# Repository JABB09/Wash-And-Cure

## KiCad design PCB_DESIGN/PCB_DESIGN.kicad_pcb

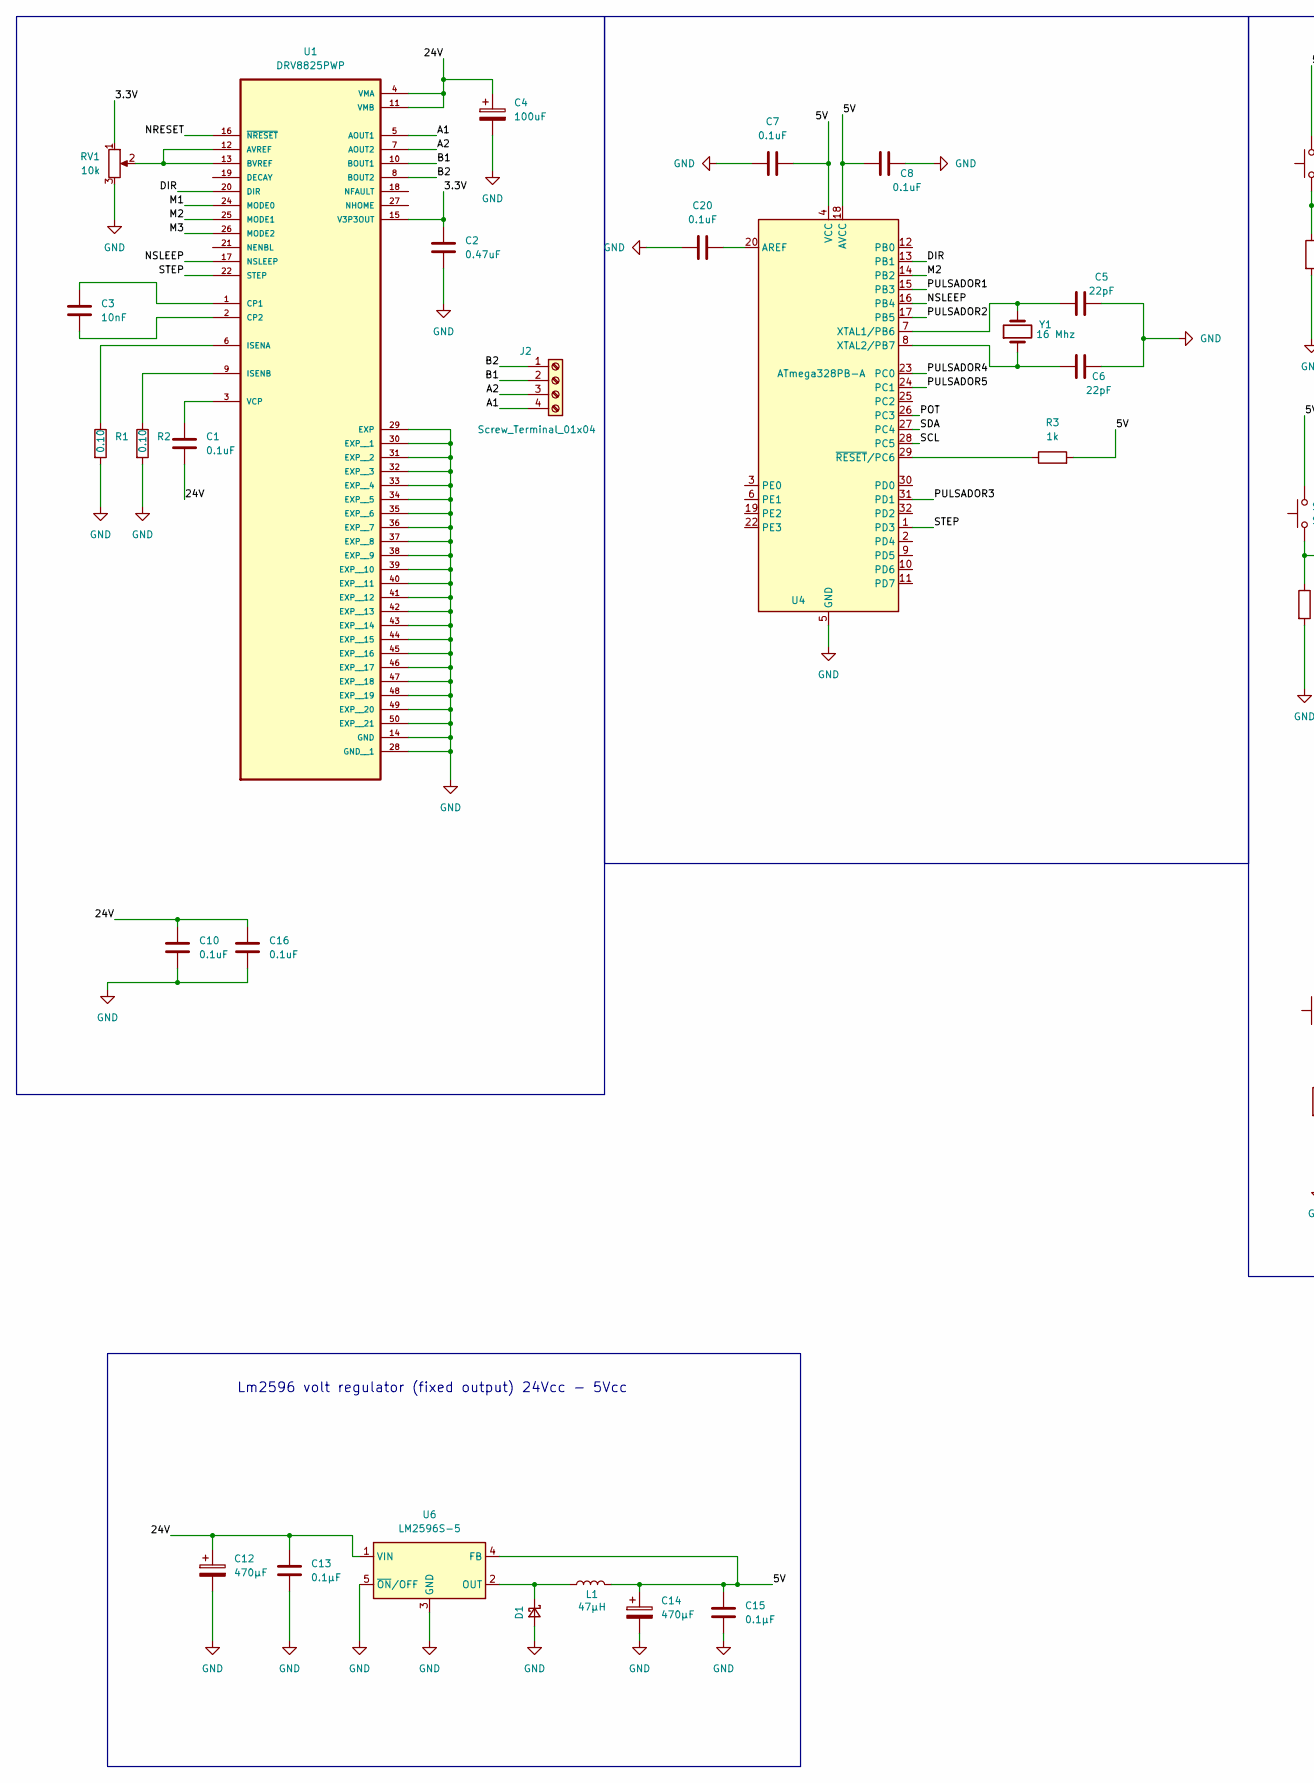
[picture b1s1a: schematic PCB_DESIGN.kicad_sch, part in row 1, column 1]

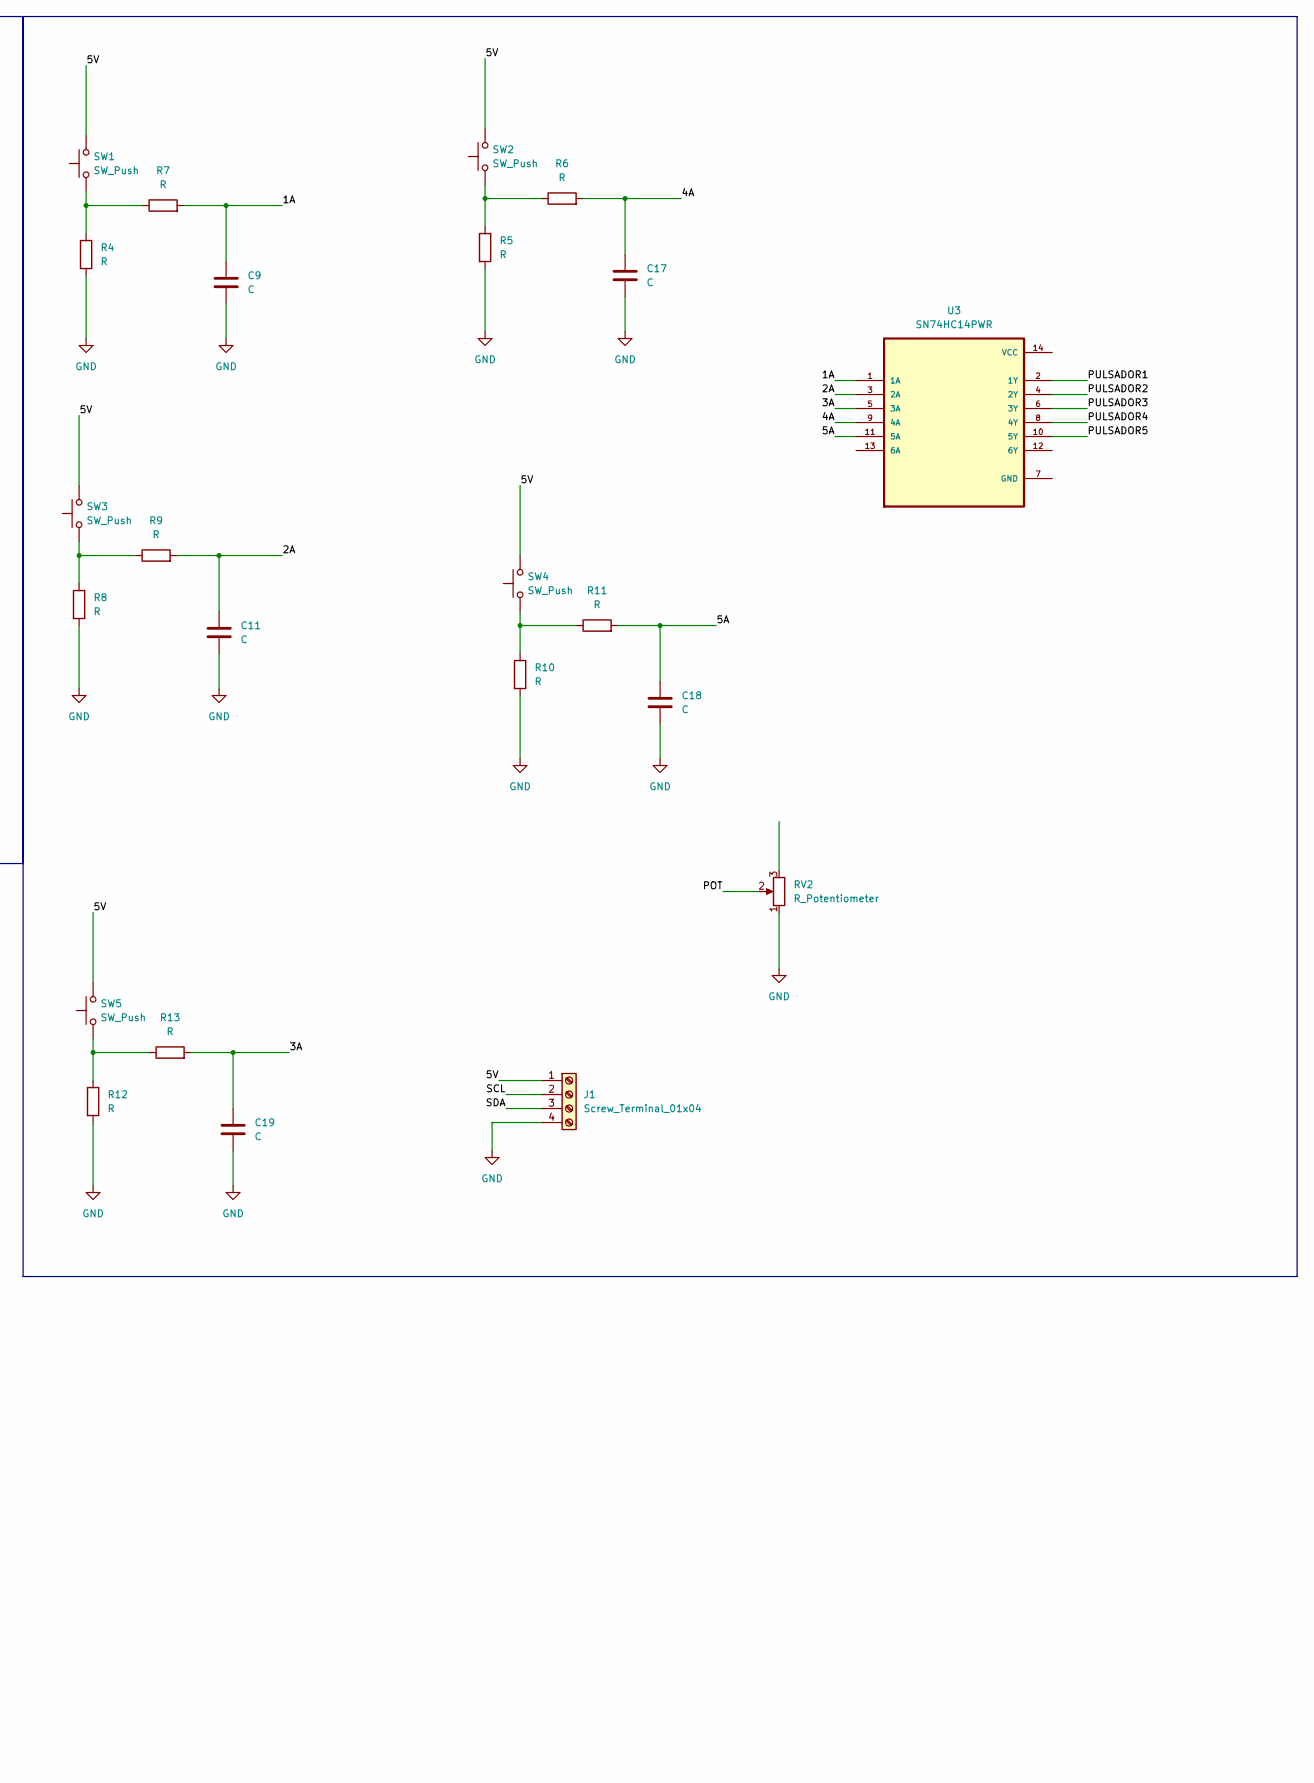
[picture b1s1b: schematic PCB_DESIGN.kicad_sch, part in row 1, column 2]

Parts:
C1, C7, C8, C10, C16, C20: 0.1uF; C_0603_1608Metric_Pad1.08x0.95mm_HandSolder
C2: 0.47uF; C_0603_1608Metric_Pad1.08x0.95mm_HandSolder
C3: 10nF; C_0603_1608Metric_Pad1.08x0.95mm_HandSolder
C4: 100uF; CP_Elec_4x5.3
C5, C6: 22pF; C_0603_1608Metric_Pad1.08x0.95mm_HandSolder
C9, C11, C17, C18, C19: C; C_0603_1608Metric_Pad1.08x0.95mm_HandSolder
C12, C14: 470μF; CP_Elec_4x5.3
C13, C15: 0.1μF; C_0603_1608Metric_Pad1.08x0.95mm_HandSolder
D1: D_Schottky_Small; D_SMA
J1, J2: Screw_Terminal_01x04; PinHeader_1x04_P2.54mm_Vertical
L1: 47μH; IND_SRR1240-470M
R1, R2: 0.10; R_0603_1608Metric_Pad0.98x0.95mm_HandSolder
R3: 1k; R_0603_1608Metric_Pad0.98x0.95mm_HandSolder
R4, R5, R6, R7, R8, R9, R10, R11, R12, R13: R; R_0603_1608Metric_Pad0.98x0.95mm_HandSolder
RV1: 10k; Potentiometer_Bourns_3314J_Vertical
RV2: R_Potentiometer; PinHeader_1x03_P2.54mm_Vertical
SW1, SW2, SW3, SW4, SW5: SW_Push; PinHeader_1x02_P2.54mm_Vertical
U1: DRV8825PWP; IC_TPS61196PWPRQ1
U3: SN74HC14PWR; SOP65P640X120-14N
U4: ATmega328PB-A; TQFP-32_7x7mm_P0.8mm
U6: LM2596S-5; TO-263-5_TabPin3
Y1: 16 Mhz; Crystal_SMD_0603-2Pin_6.0x3.5mm

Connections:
/1A: C9.2, R7.2, U3.1 (1A)
/2A: C11.2, R9.2, U3.3 (2A)
/3.3V: C2.1, RV1.1, U1.15 (V3P3OUT)
/3A: C19.2, R13.2, U3.5 (3A)
/4A: C17.2, R6.2, U3.9 (4A)
/5A: C18.2, R11.2, U3.11 (5A)
/5V: C7.2, C8.1, C14.1, C15.1, J1.1, L1.2, R3.2, SW1.2, SW2.2, SW3.2, SW4.2, SW5.2, U4.4 (VCC), U4.18 (AVCC), U6.4 (FB)
/24V: C1.2, C4.1, C10.1, C12.1, C13.1, C16.1, U1.4 (VMA), U1.11 (VMB), U6.1 (VIN)
/A1: J2.4, U1.5 (AOUT1)
/A2: J2.3, U1.7 (AOUT2)
/B1: J2.2, U1.10 (BOUT1)
/B2: J2.1, U1.8 (BOUT2)
/DIR: U1.20 (DIR), U4.13 (PB1)
/M1: U1.24 (MODE0)
/M2: U1.25 (MODE1), U4.14 (PB2)
/M3: U1.26 (MODE2)
/NRESET: U1.16 (~NRESET)
/NSLEEP: U1.17 (NSLEEP), U4.16 (PB4)
/POT: RV2.2, U4.26 (PC3)
/PULSADOR1: U3.2 (1Y), U4.15 (PB3)
/PULSADOR2: U3.4 (2Y), U4.17 (PB5)
/PULSADOR3: U3.6 (3Y), U4.31 (PD1)
/PULSADOR4: U3.8 (4Y), U4.23 (PC0)
/PULSADOR5: U3.10 (5Y), U4.24 (PC1)
/SCL: J1.2, U4.28 (PC5)
/SDA: J1.3, U4.27 (PC4)
/STEP: U1.22 (STEP), U4.1 (PD3)
GND: C2.2, C4.2, C5.2, C6.2, C7.1, C8.2, C9.1, C10.2, C11.1, C12.2, C13.2, C14.2, C15.2, C16.2, C17.1, C18.1, C19.1, C20.1, D1.2 (A), J1.4, R1.2, R2.2, R4.2, R5.2, R8.2, R10.2, R12.2, RV1.3, RV2.1, U1.14 (GND), U1.28 (GND__1), U1.29 (EXP), U1.30 (EXP__1), U1.31 (EXP__2), U1.32 (EXP__3), U1.33 (EXP__4), U1.34 (EXP__5), U1.35 (EXP__6), U1.36 (EXP__7), U1.37 (EXP__8), U1.38 (EXP__9), U1.39 (EXP__10), U1.40 (EXP__11), U1.41 (EXP__12), U1.42 (EXP__13), U1.43 (EXP__14), U1.44 (EXP__15), U1.45 (EXP__16), U1.46 (EXP__17), U1.47 (EXP__18), U1.48 (EXP__19), U1.49 (EXP__20), U1.50 (EXP__21), U4.5 (GND), U4.21 (GND), U6.3 (GND), U6.5 (~ON/OFF)
unnamed: D1.1 (K), L1.1, U6.2 (OUT)
unnamed: R4.1, R7.1, SW1.1
unnamed: R5.1, R6.1, SW2.1
unnamed: R8.1, R9.1, SW3.1
unnamed: R10.1, R11.1, SW4.1
unnamed: R12.1, R13.1, SW5.1
unnamed: RV1.2, U1.12 (AVREF), U1.13 (BVREF)
unnamed: C3.2, U1.1 (CP1)
unnamed: C3.1, U1.2 (CP2)
unnamed: R1.1, U1.6 (ISENA)
unnamed: R2.1, U1.9 (ISENB)
unnamed: C1.1, U1.3 (VCP)
unnamed: C20.2, U4.20 (AREF)
unnamed: C5.1, U4.7 (XTAL1/PB6), Y1.2
unnamed: C6.1, U4.8 (XTAL2/PB7), Y1.1
unnamed: R3.1, U4.29 (~RESET/PC6)

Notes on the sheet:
Lm2596 volt regulator (fixed output) 24Vcc - 5Vcc

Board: 2 copper layers, 49 parts (0 on the bottom side), 41 nets, no tracks yet.

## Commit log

2024-08-29 Primer Commit
2024-08-29 Se agrega submodulo de librerias al proyecto
2024-08-29 Actualización de librería
2024-08-29 Actualización submodulo
2024-09-01 Actualizacion
2024-09-01 Actualización
2024-09-05 Se actualiza el esquematico de la pcb
2024-09-05 Actualizacion de librerias
2024-09-06 Se actualiza el esquematico y se manda a pcb
2024-09-06 Actualización librería
2024-09-06 Se agregan pines de programación
2024-09-06 Actualizacion libreria
2024-09-06 Actualizacion de huellas
